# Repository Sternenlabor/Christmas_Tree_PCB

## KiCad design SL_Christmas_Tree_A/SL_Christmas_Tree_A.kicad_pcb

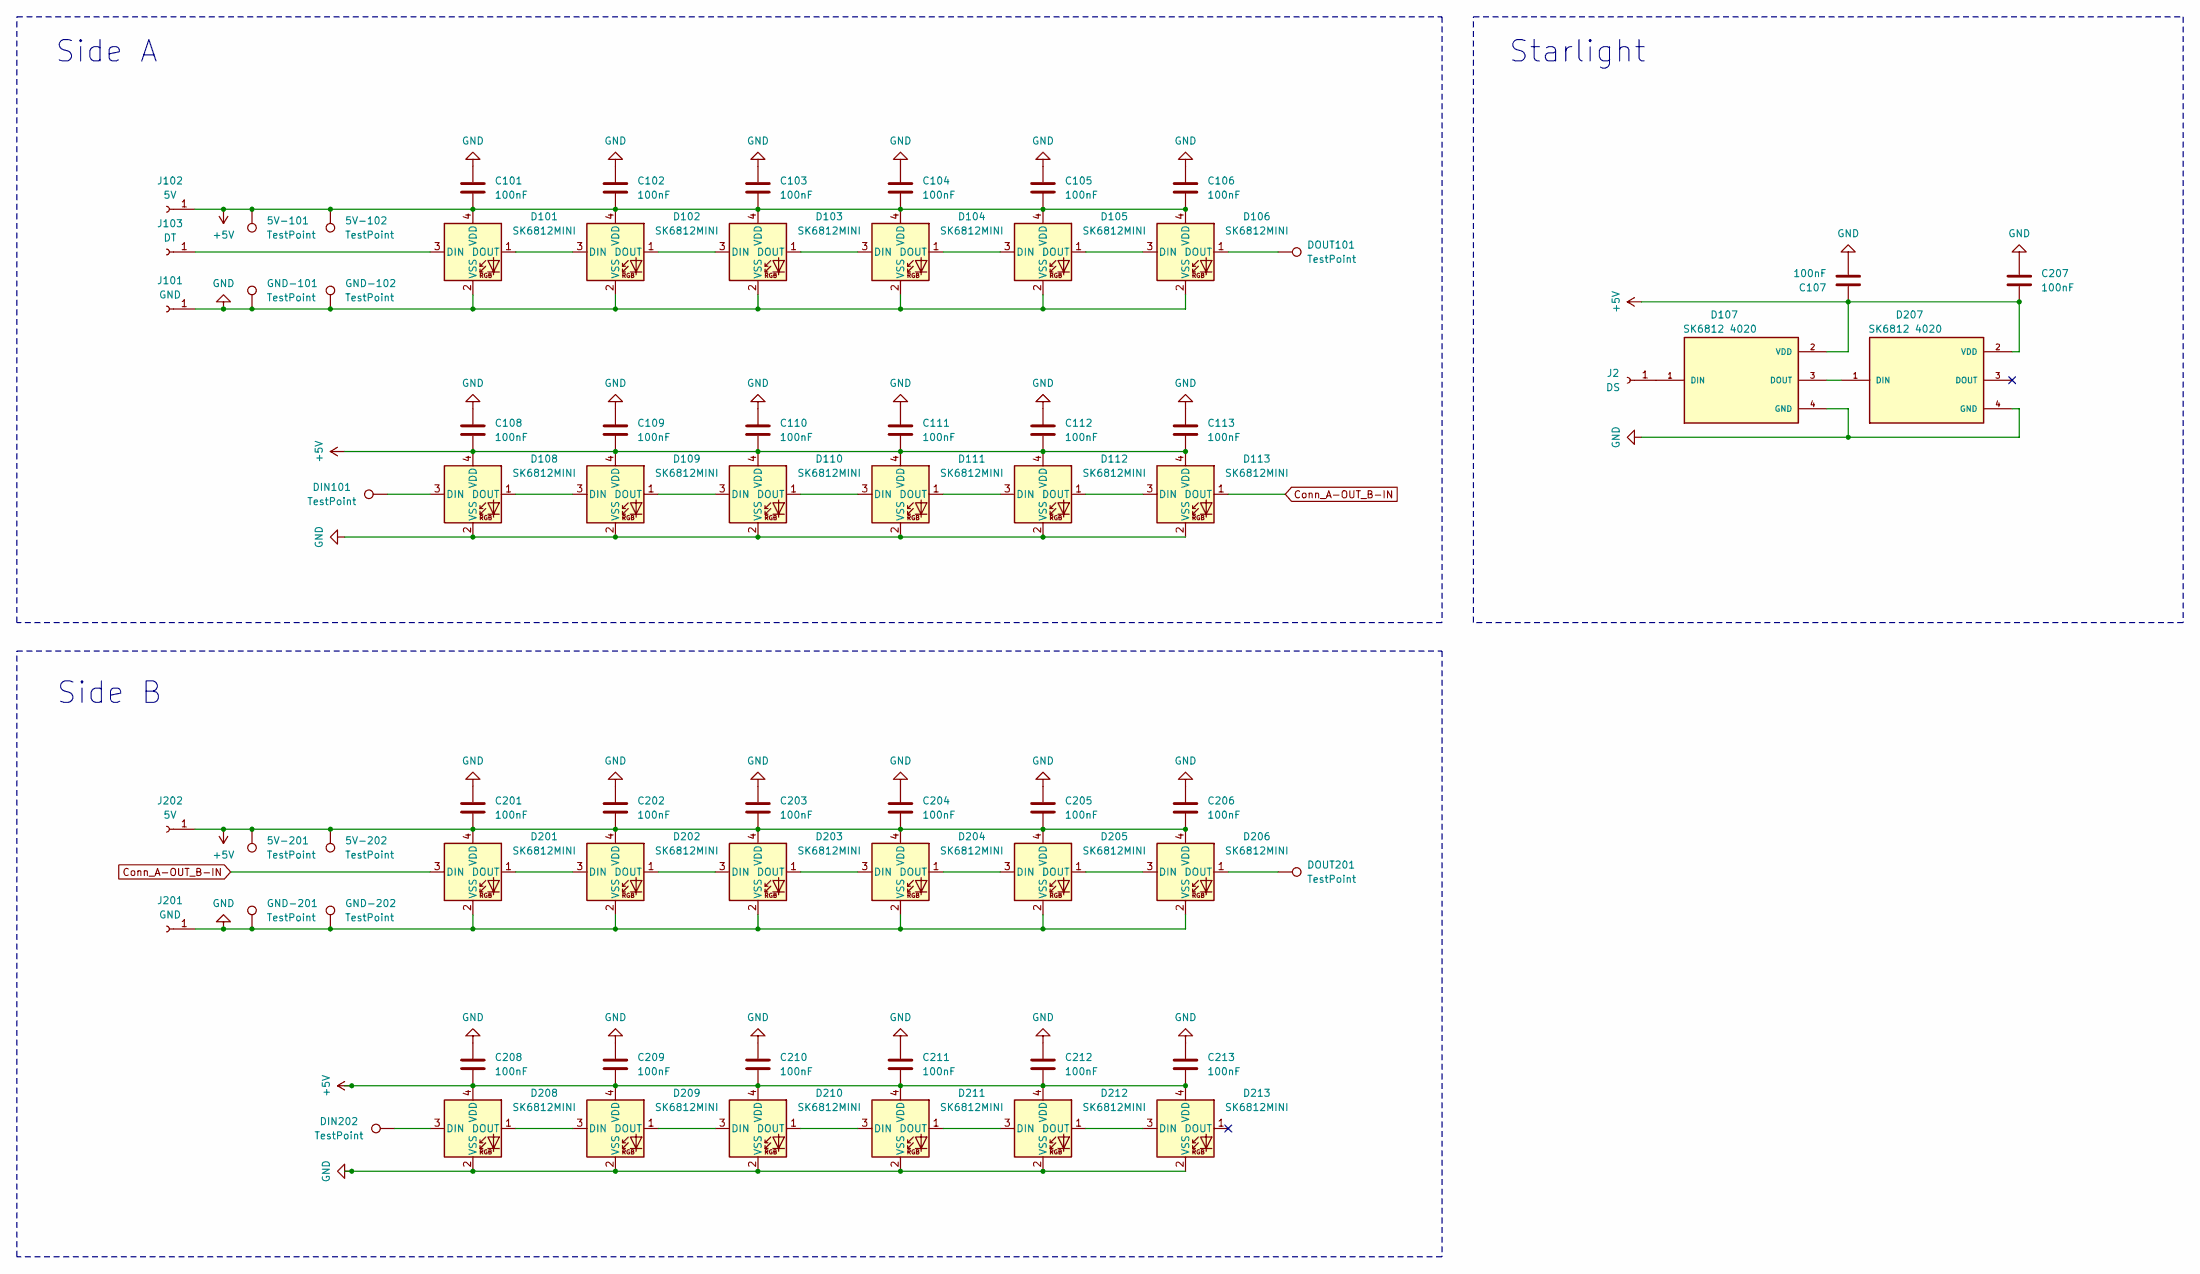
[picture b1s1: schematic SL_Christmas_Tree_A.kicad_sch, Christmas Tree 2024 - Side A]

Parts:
5V-101, 5V-102, 5V-201, 5V-202: TestPoint; TestPoint_Pad_3.0x3.0mm
C101, C102, C103, C104, C105, C106, C107, C108, C109, C110, C111, C112, C113, C201, C202, C203, C204, C205, C206, C207, C208, C209, C210, C211, C212, C213: 100nF; C_0805_2012Metric_Pad1.18x1.45mm_HandSolder
D101, D102, D103, D104, D105, D106, D108, D109, D110, D111, D112, D113, D201, D202, D203, D204, D205, D206, D208, D209, D210, D211, D212, D213: SK6812MINI; LED_SK6812MINI_PLCC4_3.5x3.5mm_P1.75mm
D107, D207: SK6812 4020; LED_SK6812_4020; PARTREV 01
DIN101, DIN202: TestPoint; TestPoint_Pad_3.0x3.0mm
DOUT101, DOUT201: TestPoint; TestPoint_Pad_3.0x3.0mm
GND-101, GND-102, GND-201, GND-202: TestPoint; TestPoint_Pad_3.0x3.0mm
J2: DS; SolderWire-1.5sqmm_1x01_D1.7mm_OD3.9mm
J101, J201: GND; SolderWire-1.5sqmm_1x01_D1.7mm_OD3.9mm
J102, J202: 5V; SolderWire-1.5sqmm_1x01_D1.7mm_OD3.9mm
J103: DT; SolderWire-1.5sqmm_1x01_D1.7mm_OD3.9mm

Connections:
+5V: 5V-101.1, 5V-102.1, 5V-201.1, 5V-202.1, C101.2, C102.2, C103.2, C104.2, C105.2, C106.2, C107.1, C108.2, C109.2, C110.2, C111.2, C112.2, C113.2, C201.2, C202.2, C203.2, C204.2, C205.2, C206.2, C207.1, C208.2, C209.2, C210.2, C211.2, C212.2, C213.2, D101.4 (VDD), D102.4 (VDD), D103.4 (VDD), D104.4 (VDD), D105.4 (VDD), D106.4 (VDD), D107.2 (VDD), D108.4 (VDD), D109.4 (VDD), D110.4 (VDD), D111.4 (VDD), D112.4 (VDD), D113.4 (VDD), D201.4 (VDD), D202.4 (VDD), D203.4 (VDD), D204.4 (VDD), D205.4 (VDD), D206.4 (VDD), D207.2 (VDD), D208.4 (VDD), D209.4 (VDD), D210.4 (VDD), D211.4 (VDD), D212.4 (VDD), D213.4 (VDD), J102.1, J202.1
Conn_A-OUT_B-IN: D113.1 (DOUT), D201.3 (DIN)
GND: C101.1, C102.1, C103.1, C104.1, C105.1, C106.1, C107.2, C108.1, C109.1, C110.1, C111.1, C112.1, C113.1, C201.1, C202.1, C203.1, C204.1, C205.1, C206.1, C207.2, C208.1, C209.1, C210.1, C211.1, C212.1, C213.1, D101.2 (VSS), D102.2 (VSS), D103.2 (VSS), D104.2 (VSS), D105.2 (VSS), D106.2 (VSS), D107.4 (GND), D108.2 (VSS), D109.2 (VSS), D110.2 (VSS), D111.2 (VSS), D112.2 (VSS), D113.2 (VSS), D201.2 (VSS), D202.2 (VSS), D203.2 (VSS), D204.2 (VSS), D205.2 (VSS), D206.2 (VSS), D207.4 (GND), D208.2 (VSS), D209.2 (VSS), D210.2 (VSS), D211.2 (VSS), D212.2 (VSS), D213.2 (VSS), GND-101.1, GND-102.1, GND-201.1, GND-202.1, J101.1, J201.1
unnamed: D101.3 (DIN), J103.1
unnamed: D101.1 (DOUT), D102.3 (DIN)
unnamed: D102.1 (DOUT), D103.3 (DIN)
unnamed: D103.1 (DOUT), D104.3 (DIN)
unnamed: D104.1 (DOUT), D105.3 (DIN)
unnamed: D105.1 (DOUT), D106.3 (DIN)
unnamed: D106.1 (DOUT), DOUT101.1
unnamed: D107.1 (DIN), J2.1
unnamed: D107.3 (DOUT), D207.1 (DIN)
unnamed: D108.3 (DIN), DIN101.1
unnamed: D108.1 (DOUT), D109.3 (DIN)
unnamed: D109.1 (DOUT), D110.3 (DIN)
unnamed: D110.1 (DOUT), D111.3 (DIN)
unnamed: D111.1 (DOUT), D112.3 (DIN)
unnamed: D112.1 (DOUT), D113.3 (DIN)
unnamed: D201.1 (DOUT), D202.3 (DIN)
unnamed: D202.1 (DOUT), D203.3 (DIN)
unnamed: D203.1 (DOUT), D204.3 (DIN)
unnamed: D204.1 (DOUT), D205.3 (DIN)
unnamed: D205.1 (DOUT), D206.3 (DIN)
unnamed: D206.1 (DOUT), DOUT201.1
unnamed: D208.3 (DIN), DIN202.1
unnamed: D208.1 (DOUT), D209.3 (DIN)
unnamed: D209.1 (DOUT), D210.3 (DIN)
unnamed: D210.1 (DOUT), D211.3 (DIN)
unnamed: D211.1 (DOUT), D212.3 (DIN)
unnamed: D212.1 (DOUT), D213.3 (DIN)

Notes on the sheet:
Starlight
Side B
Side A

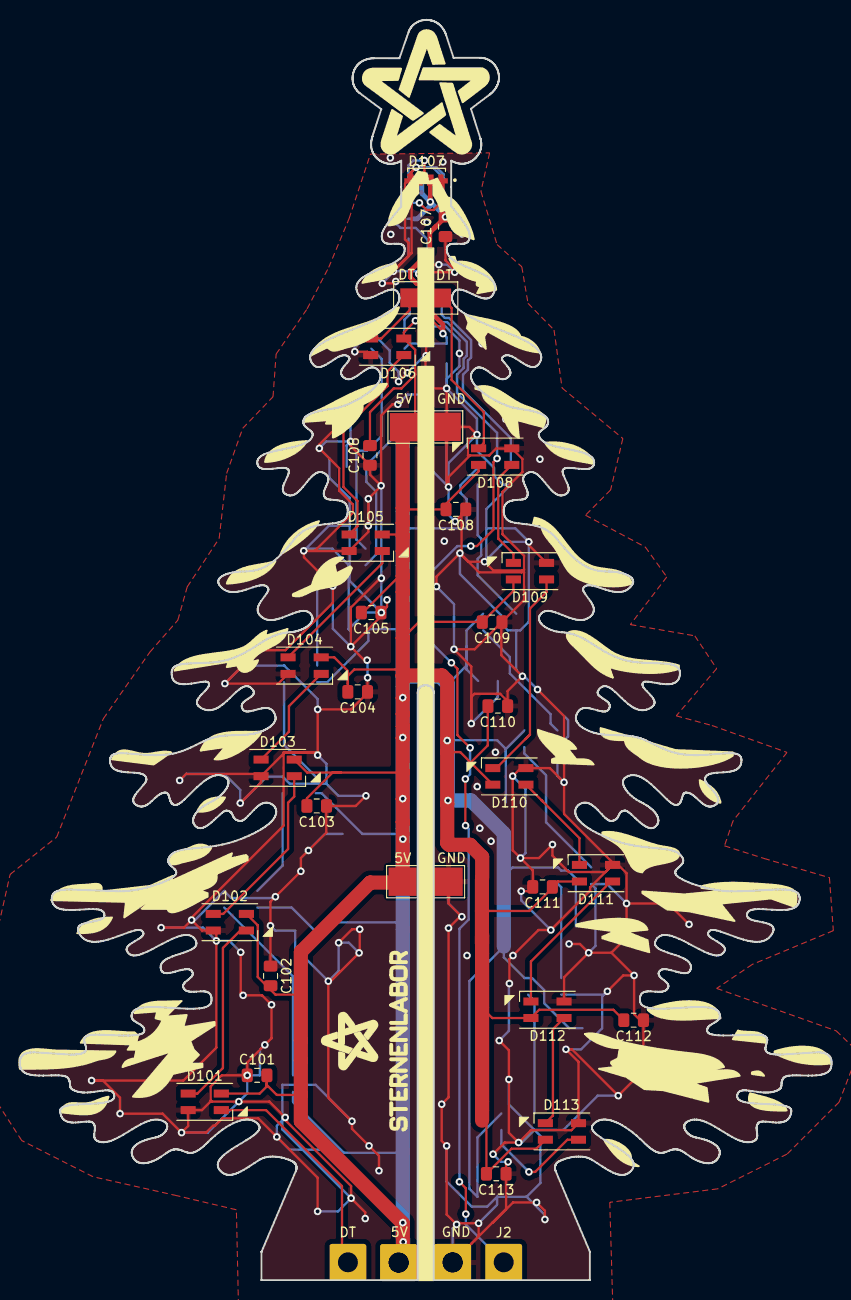
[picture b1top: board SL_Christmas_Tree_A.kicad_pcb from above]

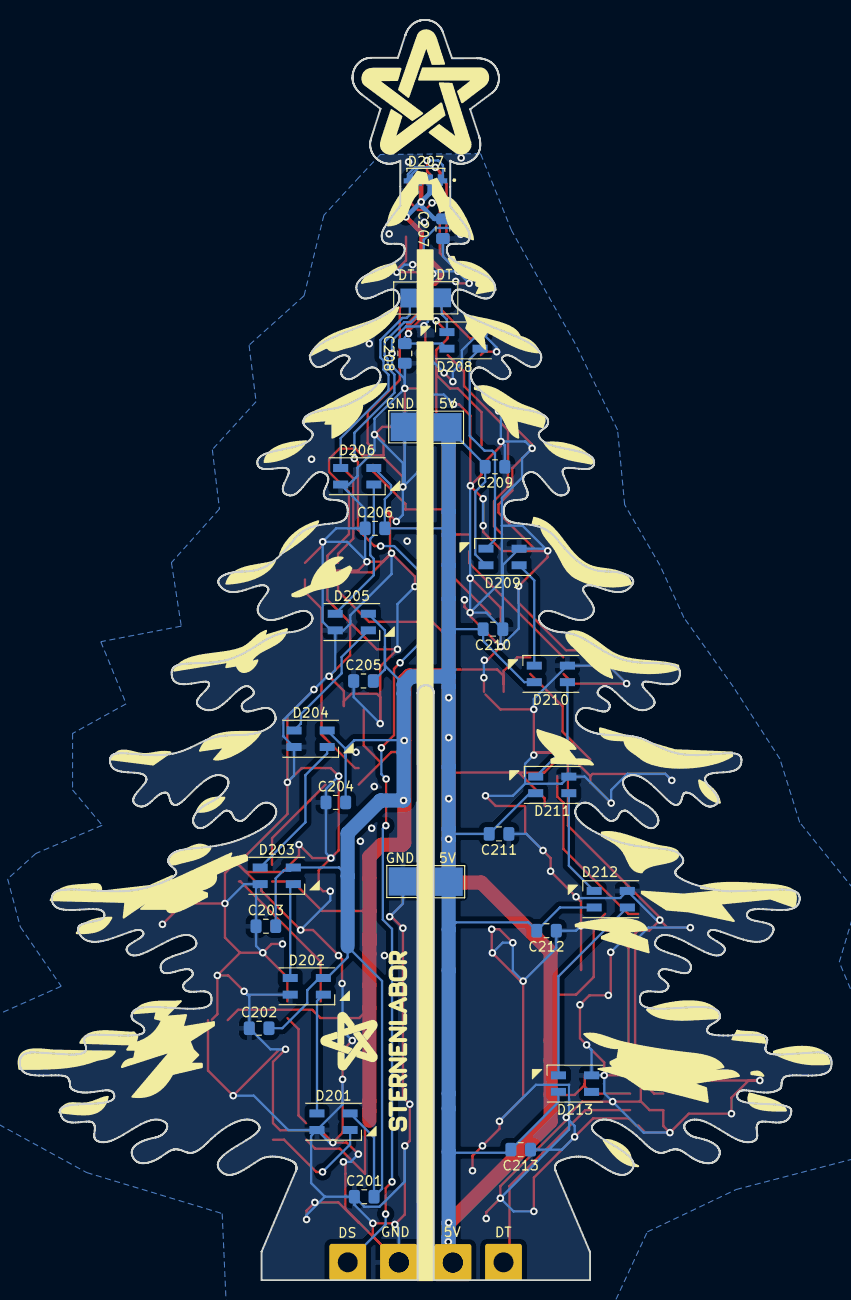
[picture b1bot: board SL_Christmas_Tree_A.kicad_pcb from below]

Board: 2 copper layers, 85.7 x 133.1 mm, 70 parts (35 on the bottom side), 30 nets.

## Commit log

2022-10-21 ignore temp files
2022-10-27 fix swapped 5V / GND
2022-11-03 added a stand
2022-11-04 fixes
2022-11-06 fix Routing
2022-11-06 fix Stand
2022-11-07 add helper for allignment
2024-10-15 PCB A v2.0
2024-10-16 remove project lock
2024-10-27 small Footprint changes and prepared "Side B" for placing parts
2024-10-27 some layout fixes
2024-10-30 WIP v2.1
2024-11-01 v2.1 Final
2024-11-10 Fix routing issues on PCB A
2024-11-27 Stand for Wemos D1 Mini (Type-C)
2024-12-03 Christmas Tree WLED Setup
